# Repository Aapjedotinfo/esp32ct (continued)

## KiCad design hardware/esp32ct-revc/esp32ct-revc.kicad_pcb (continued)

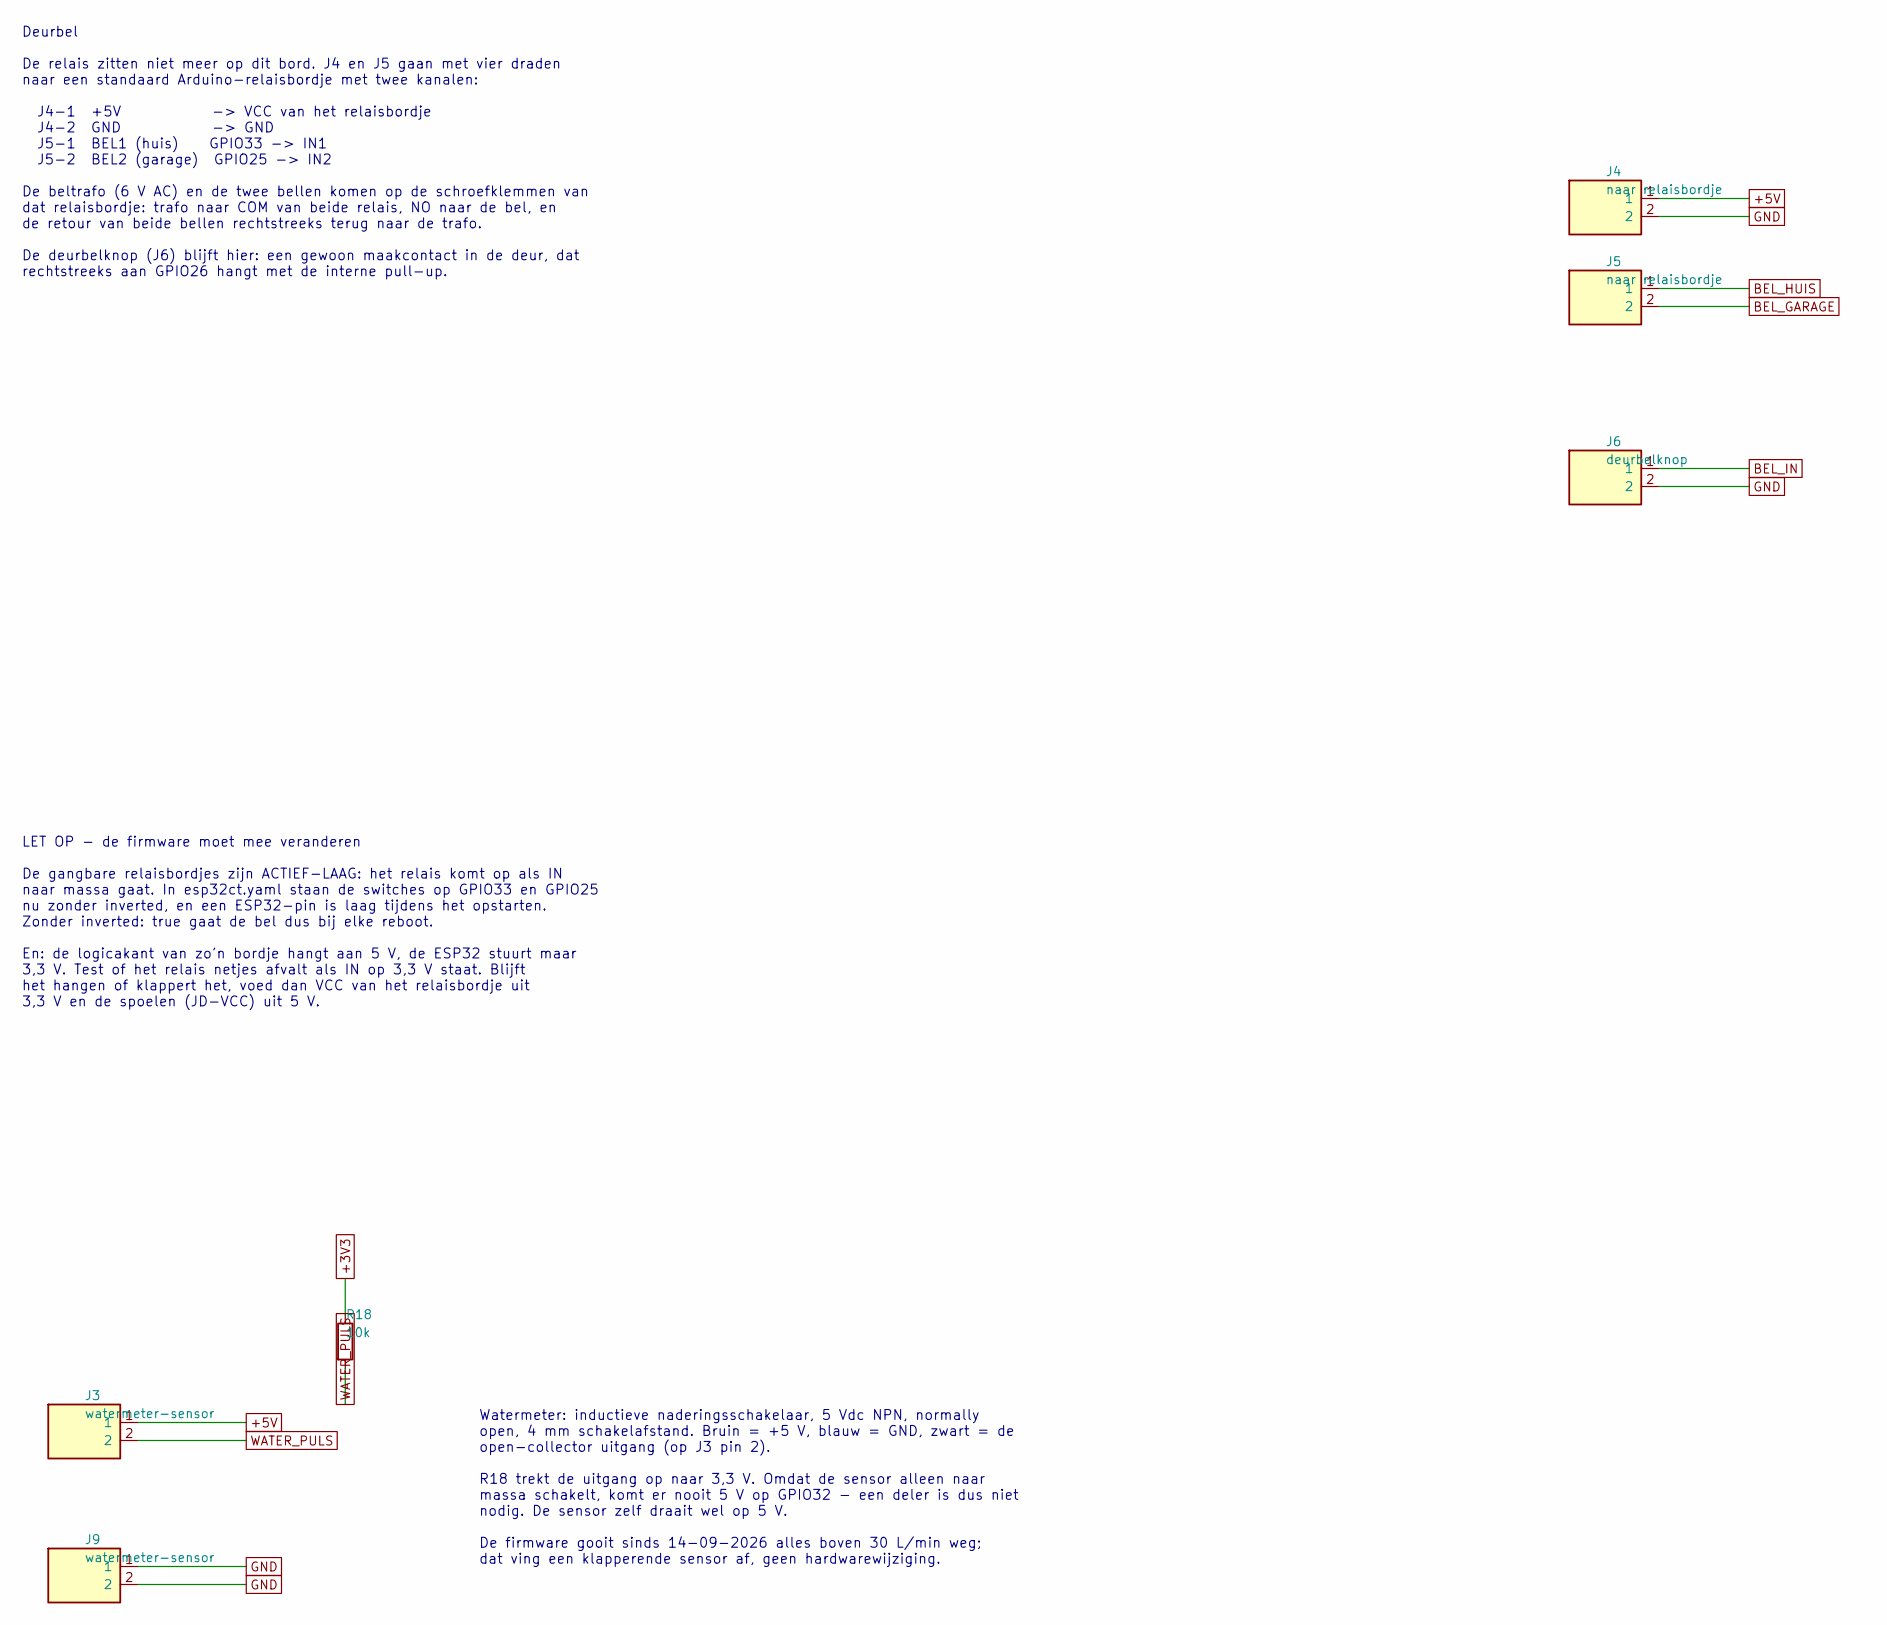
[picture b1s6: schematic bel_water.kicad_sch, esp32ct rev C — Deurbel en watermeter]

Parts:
J3, J9: watermeter-sensor; MX126_2P_5mm_krap
J4, J5: naar relaisbordje; MX126_2P_5mm_krap
J6: deurbelknop; MX126_2P_5mm_krap
R18: 10k; R_Axial_DIN0207_L6.3mm_D2.5mm_P10.16mm_Horizontal

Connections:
+3V3: R18.1; also elsewhere on the board
+5V: J3.1, J4.1; also elsewhere on the board
BEL_GARAGE: J5.2; also elsewhere on the board
BEL_HUIS: J5.1; also elsewhere on the board
BEL_IN: J6.1; also elsewhere on the board
GND: J4.2, J6.2, J9.1, J9.2; also elsewhere on the board
WATER_PULS: J3.2, R18.2; also elsewhere on the board

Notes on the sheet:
Watermeter: inductieve naderingsschakelaar, 5 Vdc NPN, normally open, 4 mm schakelafstand. Bruin = +5 V, blauw = GND, zwart = de open-collector uitgang (op J3 pin 2). R18 trekt de uitgang op naar 3,3 V. Omdat de sensor alleen naar massa schakelt, komt er nooit 5 V op GPIO32 - een deler is dus niet 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
Deurbel De relais zitten niet meer op dit bord. J4 en J5 gaan met vier draden naar een standaard Arduino-relaisbordje met twee kanalen: J4-1 +5V -> VCC van het relaisbordje J4-2 GND -> GND J5-1 BEL1 (huis) GPIO33 -> IN1 J5-2 BEL2 (garage) GPIO25 -> IN2 De beltrafo (6 V AC) en de twee bellen komen o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
LET OP - de firmware moet mee veranderen De gangbare relaisbordjes zijn ACTIEF-LAAG: het relais komt op als IN naar massa gaat. In esp32ct.yaml staan de switches op GPIO33 en GPIO25 nu zonder inverted, en een ESP32-pin is laag tijdens het opstarten. Zonder inverted: true gaat de bel dus bij elke re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

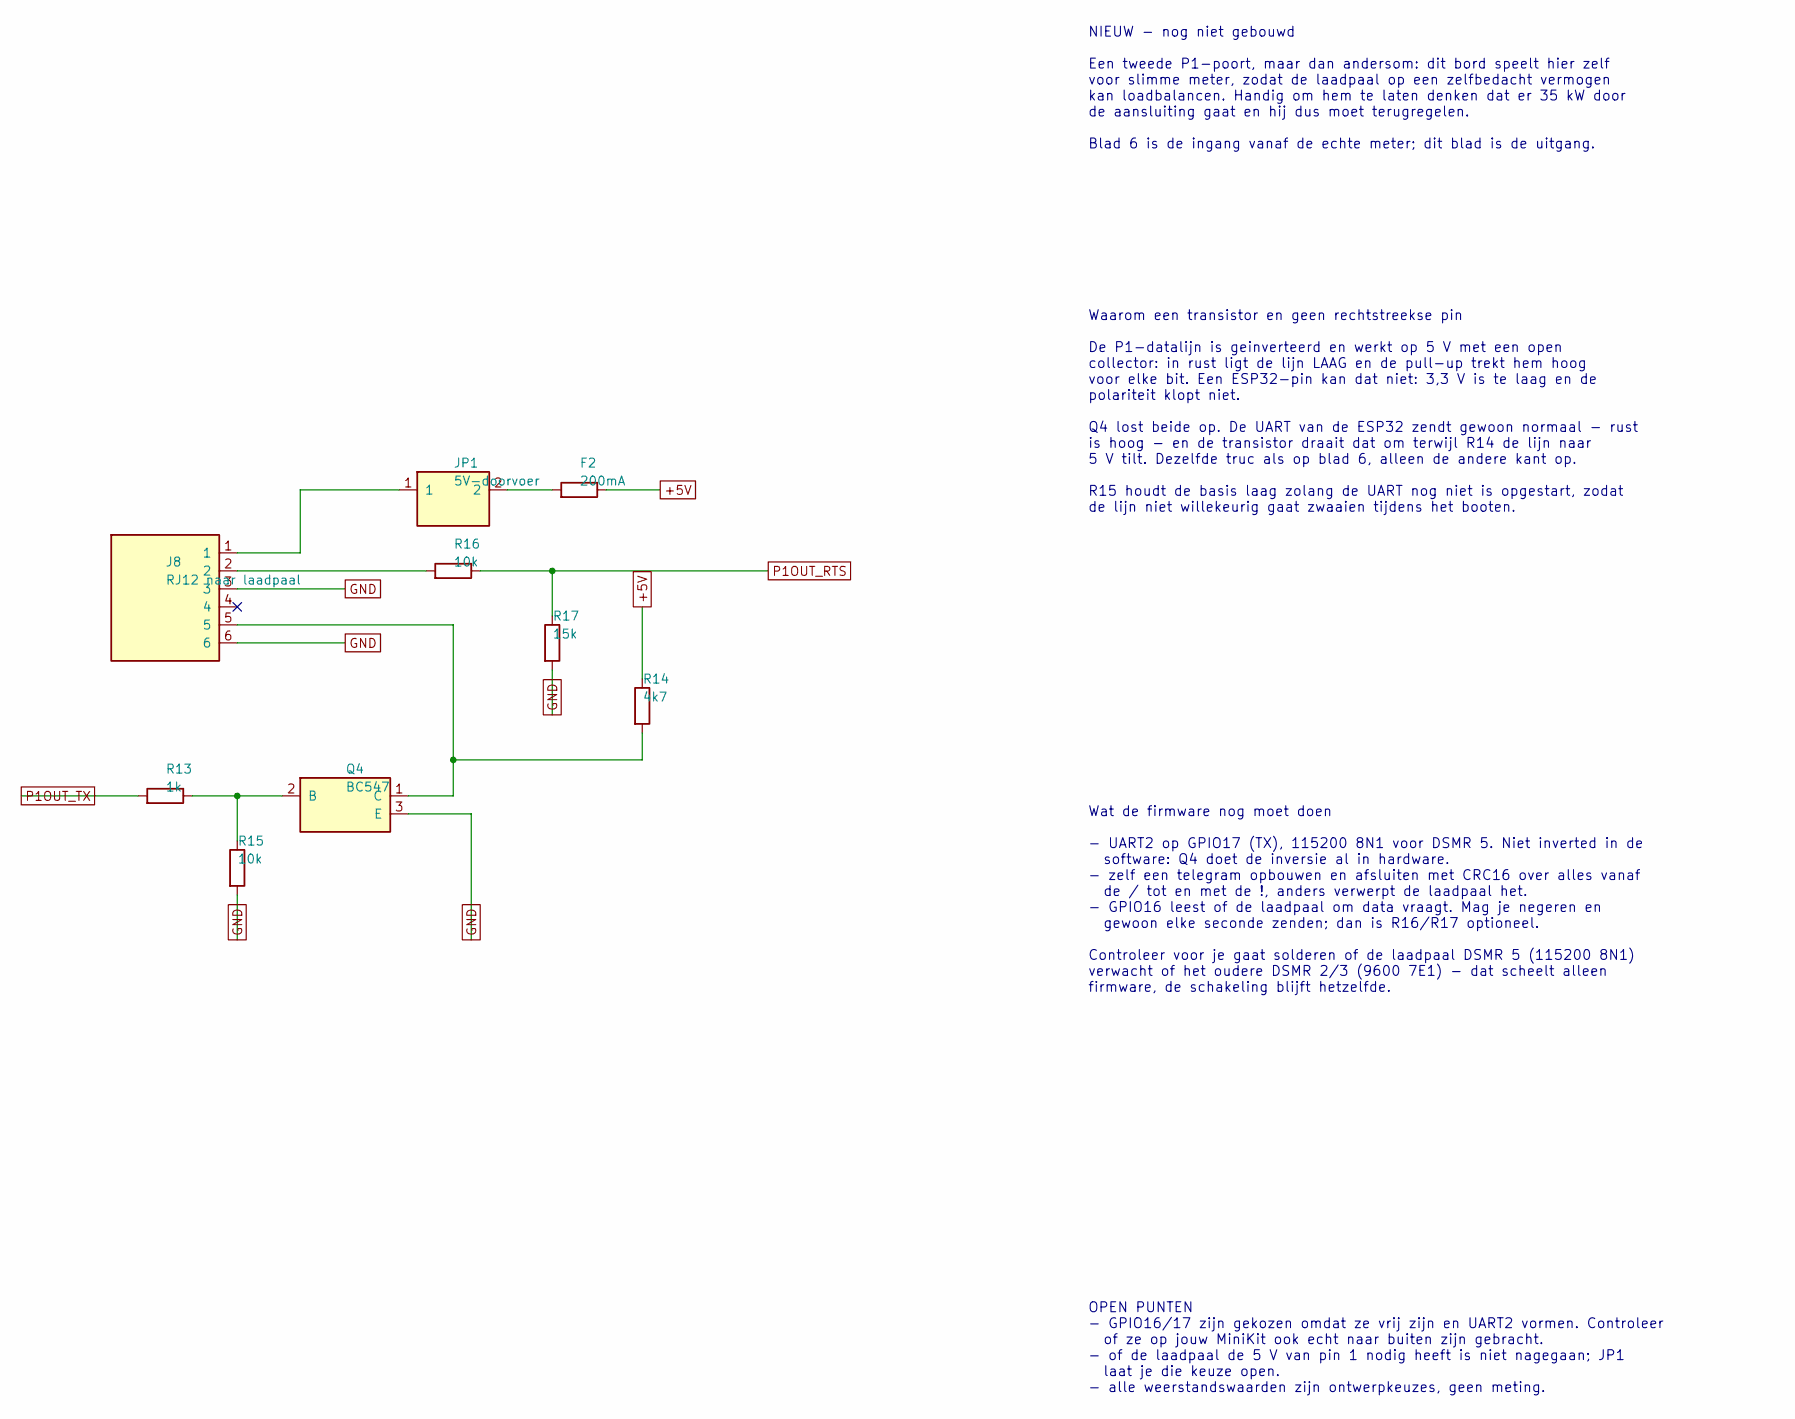
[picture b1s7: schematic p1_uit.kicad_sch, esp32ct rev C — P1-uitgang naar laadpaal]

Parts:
F2: 200mA; R_Axial_DIN0207_L6.3mm_D2.5mm_P10.16mm_Horizontal
J8: RJ12 naar laadpaal; RJ12_Amphenol_54601-x06_Horizontal
JP1: 5V-doorvoer; PinHeader_1x02_P2.54mm_Vertical
Q4: BC547; TO-92_Inline_Wide
R13: 1k; R_Axial_DIN0207_L6.3mm_D2.5mm_P10.16mm_Horizontal
R14: 4k7; R_Axial_DIN0207_L6.3mm_D2.5mm_P10.16mm_Horizontal
R15, R16: 10k; R_Axial_DIN0207_L6.3mm_D2.5mm_P10.16mm_Horizontal
R17: 15k; R_Axial_DIN0207_L6.3mm_D2.5mm_P10.16mm_Horizontal

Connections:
+5V: F2.2, R14.1; also elsewhere on the board
GND: J8.3, J8.6, Q4.3 (E), R15.2, R17.2; also elsewhere on the board
unnamed: F2.1, JP1.2
unnamed: J8.1, JP1.1
unnamed: J8.2, R16.1
unnamed: Q4.2 (B), R13.2, R15.1
unnamed: J8.5, Q4.1 (C), R14.2
P1OUT_RTS: R16.2, R17.1; also elsewhere on the board
P1OUT_TX: R13.1; also elsewhere on the board

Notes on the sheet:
NIEUW - nog niet gebouwd Een tweede P1-poort, maar dan andersom: dit bord speelt hier zelf voor slimme meter, zodat de laadpaal op een zelfbedacht vermogen kan loadbalancen. Handig om hem te laten denken dat er 35 kW door de aansluiting gaat en hij dus moet terugregelen. Blad 6 is de ingang vanaf d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
Waarom een transistor en geen rechtstreekse pin De P1-datalijn is geinverteerd en werkt op 5 V met een open collector: in rust ligt de lijn LAAG en de pull-up trekt hem hoog voor elke bit. Een ESP32-pin kan dat niet: 3,3 V is te laag en de polariteit klopt niet. Q4 lost beide op. De UART van de ESP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
Wat de firmware nog moet doen - UART2 op GPIO17 (TX), 115200 8N1 voor DSMR 5. Niet inverted in de software: Q4 doet de inversie al in hardware. - zelf een telegram opbouwen en afsluiten met CRC16 over alles vanaf de / tot en met de !, anders verwerpt de laadpaal het. - GPIO16 leest of de laadpaal o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
OPEN PUNTEN - GPIO16/17 zijn gekozen omdat ze vrij zijn en UART2 vormen. Controleer of ze op jouw MiniKit ook echt naar buiten zijn gebracht. - of de laadpaal de 5 V van pin 1 nodig heeft is niet nagegaan; JP1 laat je die keuze open. - alle weerstandswaarden zijn ontwerpkeuzes, geen meting.

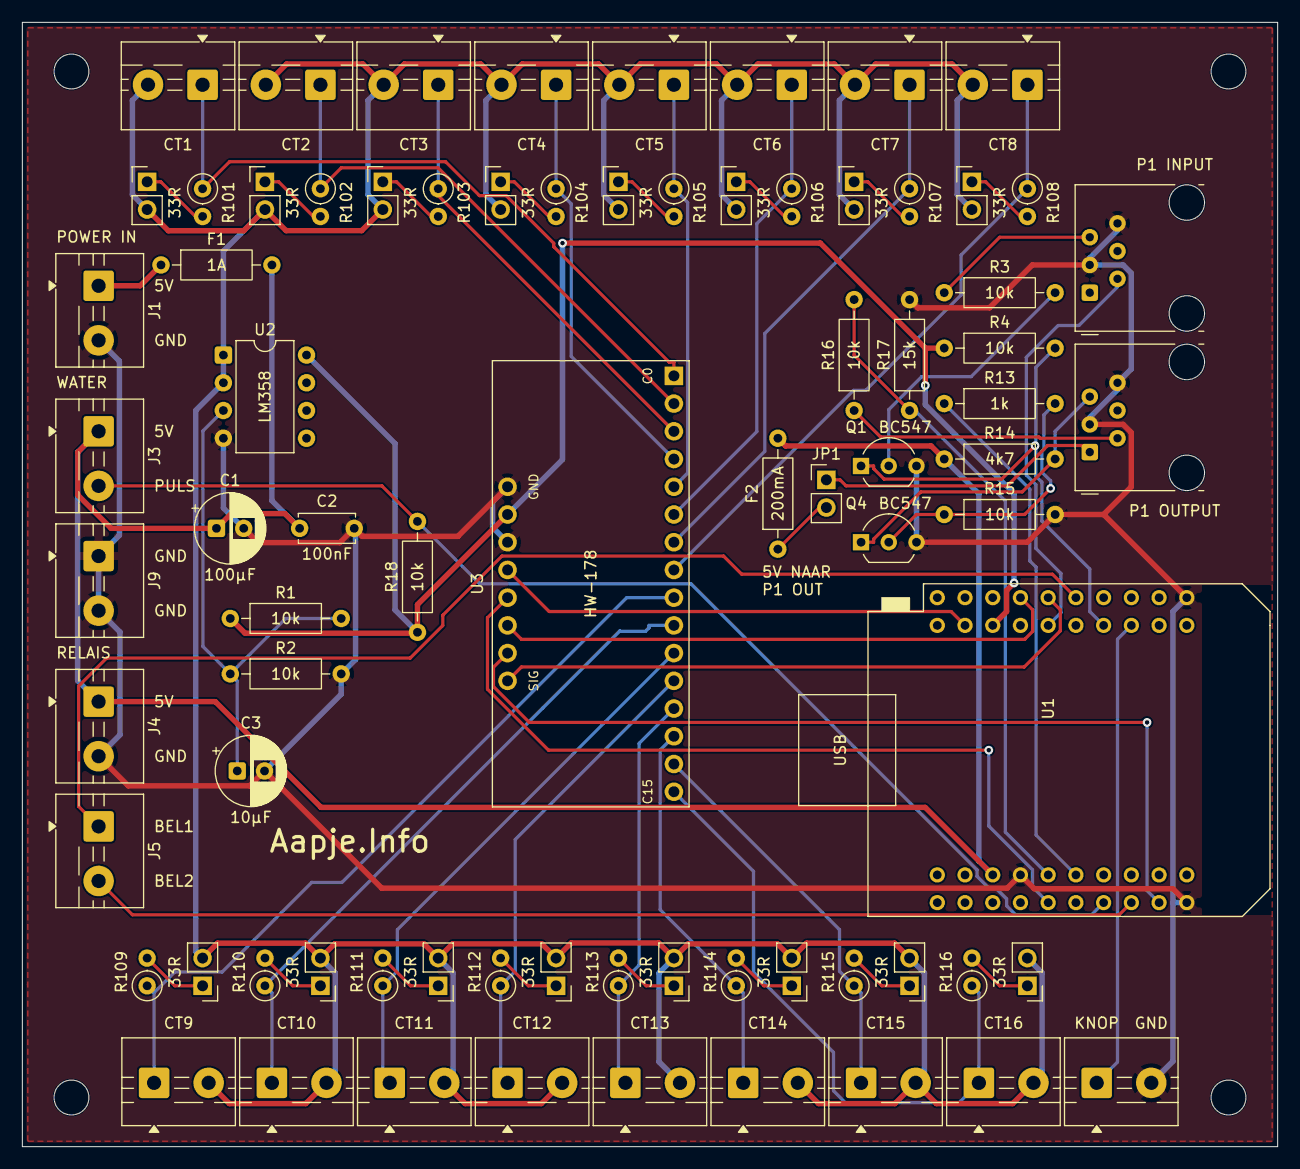
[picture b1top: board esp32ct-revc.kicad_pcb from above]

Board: 2 copper layers, 115.0 x 103.0 mm, 81 parts (0 on the bottom side), 58 nets.

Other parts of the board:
H1, H2, H3, H4: M3; MountingHole_3.2mm_M3

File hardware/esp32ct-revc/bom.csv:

"Reference","Value","Description","Footprint"
"C1","100u (?)","","Capacitor_THT:CP_Radial_D6.3mm_P2.50mm"
"C2","100n (?)","","Capacitor_THT:C_Disc_D5.0mm_W2.5mm_P5.00mm"
"C3","10u (?)","dempt de middenrail","Capacitor_THT:CP_Radial_D6.3mm_P2.50mm"
"F1","1A","zekering 1 A traag, axiaal; of een 0 ohm-brug","Resistor_THT:R_Axial_DIN0207_L6.3mm_D2.5mm_P10.16mm_Horizontal"
"F2","200mA","zekering 200 mA naar de laadpaal, axiaal; of een 0 ohm-brug","Resistor_THT:R_Axial_DIN0207_L6.3mm_D2.5mm_P10.16mm_Horizontal"
"J1","+5V extern","externe 5 V voeding van het bord","esp32ct:MX126_2P_5mm_krap"
"J2","RJ12 naar slimme meter","P1-poort, DSMR 5","Connector_RJ:RJ12_Amphenol_54601-x06_Horizontal"
"J3,J9","watermeter-sensor","pulssensor op de watermeter","esp32ct:MX126_2P_5mm_krap"
"J4","naar relaisbordje","voeding van het relaisbordje (VCC/GND)","esp32ct:MX126_2P_5mm_krap"
"J5","naar relaisbordje","stuurlijnen naar IN1/IN2","esp32ct:MX126_2P_5mm_krap"
"J6","deurbelknop","maakcontact in de deur, potentiaalvrij","esp32ct:MX126_2P_5mm_krap"
"J8","RJ12 naar laadpaal","NIEUW - nagebootste P1-poort, nog niet gebouwd","Connector_RJ:RJ12_Amphenol_54601-x06_Horizontal"
"J11","CT1","CT-klem of ringkern","esp32ct:MX126_2P_5mm_krap"
"J12","CT2","CT-klem of ringkern","esp32ct:MX126_2P_5mm_krap"
"J13","CT3","CT-klem of ringkern","esp32ct:MX126_2P_5mm_krap"
"J14","CT4","CT-klem of ringkern","esp32ct:MX126_2P_5mm_krap"
"J15","CT5","CT-klem of ringkern","esp32ct:MX126_2P_5mm_krap"
"J16","CT6","CT-klem of ringkern","esp32ct:MX126_2P_5mm_krap"
"J17","CT7","CT-klem of ringkern","esp32ct:MX126_2P_5mm_krap"
"J18","CT8","CT-klem of ringkern","esp32ct:MX126_2P_5mm_krap"
"J19","CT9","CT-klem of ringkern","esp32ct:MX126_2P_5mm_krap"
"J20","CT10","CT-klem of ringkern","esp32ct:MX126_2P_5mm_krap"
"J21","CT11","CT-klem of ringkern","esp32ct:MX126_2P_5mm_krap"
"J22","CT12","CT-klem of ringkern","esp32ct:MX126_2P_5mm_krap"
"J23","CT13","CT-klem of ringkern","esp32ct:MX126_2P_5mm_krap"
"J24","CT14","CT-klem of ringkern","esp32ct:MX126_2P_5mm_krap"
"J25","CT15","CT-klem of ringkern","esp32ct:MX126_2P_5mm_krap"
"J26","CT16","CT-klem of ringkern","esp32ct:MX126_2P_5mm_krap"
"JP1","5V-doorvoer","open laten als de laadpaal zichzelf voedt","Connector_PinHeader_2.54mm:PinHeader_1x02_P2.54mm_Vertical"
"JP101-JP116","burden","dicht: burden actief. open: klem heeft eigen burden","Connector_PinHeader_2.54mm:PinHeader_1x02_P2.54mm_Vertical"
"Q1","BC547 (?)","inverteert het open-collector datasignaal van de meter","Package_TO_SOT_THT:TO-92_Inline_Wide"
"Q4","BC547","maakt het geinverteerde open-collector signaal","Package_TO_SOT_THT:TO-92_Inline_Wide"
"R1","10k (?)","bovenste helft van de 1,65 V deler","Resistor_THT:R_Axial_DIN0207_L6.3mm_D2.5mm_P10.16mm_Horizontal"
"R2","10k (?)","onderste helft van de 1,65 V deler","Resistor_THT:R_Axial_DIN0207_L6.3mm_D2.5mm_P10.16mm_Horizontal"
"R3,R4","10k (?)","","Resistor_THT:R_Axial_DIN0207_L6.3mm_D2.5mm_P10.16mm_Horizontal"
"R13","1k","","Resistor_THT:R_Axial_DIN0207_L6.3mm_D2.5mm_P10.16mm_Horizontal"
"R14","4k7","pull-up; bij 115200 baud niet hoger kiezen","Resistor_THT:R_Axial_DIN0207_L6.3mm_D2.5mm_P10.16mm_Horizontal"
"R15","10k","houdt de basis laag als de ESP32 nog niet zendt","Resistor_THT:R_Axial_DIN0207_L6.3mm_D2.5mm_P10.16mm_Horizontal"
"R16","10k","","Resistor_THT:R_Axial_DIN0207_L6.3mm_D2.5mm_P10.16mm_Horizontal"
"R17","15k","onderste helft van de 5V->3V3 deler","Resistor_THT:R_Axial_DIN0207_L6.3mm_D2.5mm_P10.16mm_Horizontal"
"R18","10k","pull-up watermeterpuls naar 3,3 V","Resistor_THT:R_Axial_DIN0207_L6.3mm_D2.5mm_P10.16mm_Horizontal"
"R101-R116","33R","burden 33R -> 0,033 V/A theoretisch, 0,0307 V/A gefit","Resistor_THT:R_Axial_DIN0207_L6.3mm_D2.5mm_P2.54mm_Vertical"
"U1","MH-ET Live D1 mini ESP32","ESP32-WROOM-32, 4 MB flash","esp32ct:ESP32_mini"
"U2","LM358","opamp als spanningsvolger op de 1,65 V middenrail","Package_DIP:DIP-8_W7.62mm"
"U3","HW-178 (CD74HC4067)","voetje voor het HW-178-breakout, plat op twee female headers","esp32ct:HW178_socket"

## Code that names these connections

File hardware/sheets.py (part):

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    sh.wire(jr, (jr[0] + g(3), jr[1]), (jr[0] + g(3), retour[1]), retour)
    sh.wire(retour, p2)
    sh.wire(retour, (retour[0] - g(10), retour[1]))
    sh.label("VBIAS", (retour[0] - g(10), retour[1]), 180)
    sh.junction(retour)


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        "esp32ct rev C — 16 CT-kanalen, P1 in en uit, watermeter, deurbel\n\n"
        "ONTWERP. Basis is het huidige bord; de wijzigingen staan hieronder.\n\n"
        "De pinbezetting komt uit de draaiende firmware (esp32ct.yaml), met\n"
        "twee wijzigingen: P1_RTS van GPIO19 naar GPIO23, en mux S1 van\n"
        "GPIO12 naar GPIO4. Nieuw zijn GPIO16 en GPIO17 voor de P1-uitgang.\n\n"
        "Geen strapping pins: GPIO0, 2, 5, 12 en 15 hangen nergens aan.\n"
        "Een hoge GPIO12 bij het opstarten zet de flash op 1,8 V en dan\n"
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        "- de relais zitten op een los Arduino-relaisbordje (J4/J5).\n"
        "  Die zijn actief-laag: de firmware heeft inverted: true nodig.\n"
        "- nieuw: P1-uitgang naar de laadpaal (blad 7).\n"
        "- P1_RTS op GPIO23 (was 19), mux S1 op GPIO4 (was 12).\n"
        "GPIO35 komt vrij.", 20, 195, 1.4)

    y = 60
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    voed.wire(out, (out[0] + 7.62, out[1]), (out[0] + 7.62, out[1] - 12.7),
              (im[0] - 7.62, out[1] - 12.7), (im[0] - 7.62, im[1]), im)
    voed.wire(out, (out[0] + 17.78, out[1]))
    voed.label("VBIAS", (out[0] + 17.78, out[1]))
    vp, vm = voed.at(u2, "8"), voed.at(u2, "4")
    voed.wire(vp, (vp[0] + 7.62, vp[1]))
    voed.label("+3V3", (vp[0] + 7.62, vp[1]))
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        mux.label(f"CT{i + 1}", (p[0] - g(8), p[1]), 180)
    ps = mux.at(u3, "17")
    mux.wire(ps, (ps[0] + g(10), ps[1]))
    mux.label("SIG_MUX1", (ps[0] + g(10), ps[1]))
    pe = mux.at(u3, "18")
    mux.wire(pe, (pe[0] + g(10), pe[1]))
    mux.label("GND", (pe[0] + g(10), pe[1]))
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    bb = p1s.at(q1, "2")
    p1s.wire(p1s.at(rb, "2"), bb)
    p1s.wire(p1s.at(rb, "1"), (p1s.at(rb, "1")[0] - 10.16, bb[1]))
    p1s.label("P1_DATA", (p1s.at(rb, "1")[0] - 10.16, bb[1]), 180)
    cc, ee = p1s.at(q1, "1"), p1s.at(q1, "3")
    p1s.wire(ee, (ee[0] + 7.62, ee[1]), (ee[0] + 7.62, ee[1] + 7.62))
    p1s.label("GND", (ee[0] + 7.62, ee[1] + 7.62), 270)
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    p1s.wire(rpt, (rpt[0], rpt[1] - 7.62))
    p1s.label("+3V3", (rpt[0], rpt[1] - 7.62), 90)
    p1s.wire((rpb[0], cc[1]), (rpb[0] + 15.24, cc[1]))
    p1s.label("P1_RX", (rpb[0] + 15.24, cc[1]))
    p1s.junction((rpb[0], cc[1]))

    p1s.note(
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        "De meter zendt inverted TTL op een open-collector uitgang. Een NPN\n"
        "draait het signaal om en tilt het naar 3,3 V, zodat de UART van de\n"
        "ESP32 het kan lezen (GPIO18).\n\n"
        "P1_RTS (GPIO23) vraagt de meter om te zenden: hoog is elke seconde\n"
        "een telegram. De firmware heeft dit als request_pin.", 240, 40, 1.4)

    p1s.note(
        "OPEN PUNTEN op dit blad\n"
        "- de inverter is de gangbare schakeling, maar het type transistor\n"
        "  en de weerstandswaarden zijn NIET van het bord afgelezen\n"
        "- of P1_RTS rechtstreeks aan GPIO23 mag of via een\n"
        "  niveauomzetter naar 5 V, is niet nagekeken\n"
        "- of de meter het bord voedt via RJ12 pin 1 is niet nagekeken;\n"
        "  hier is uitgegaan van de externe 5 V op J1", 240, 120, 1.4)
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    p1u.wire(p1u.at(r17, "2"), (knoop[0], g(100)))
    p1u.label("GND", (knoop[0], g(100)), 270)
    p1u.wire(knoop, (g(122), knoop[1]))
    p1u.label("P1OUT_RTS", (g(122), knoop[1]))

    # pin 3 en 6: massa. pin 4 is ongebruikt.
    for num in ("3", "6"):
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
    r13 = p1u.sym("R_H", "R13", "1k", g(55), qb[1])
    p1u.wire(p1u.at(r13, "1"), (g(39), qb[1]))
    p1u.label("P1OUT_TX", (g(39), qb[1]), 180)
    basis = (g(63), qb[1])
    p1u.wire(p1u.at(r13, "2"), basis)
    p1u.wire(basis, qb)
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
